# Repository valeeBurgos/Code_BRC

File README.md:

# Code_BRC

Placa y código funcional pero con ciertos fallos  para un robot velocista.

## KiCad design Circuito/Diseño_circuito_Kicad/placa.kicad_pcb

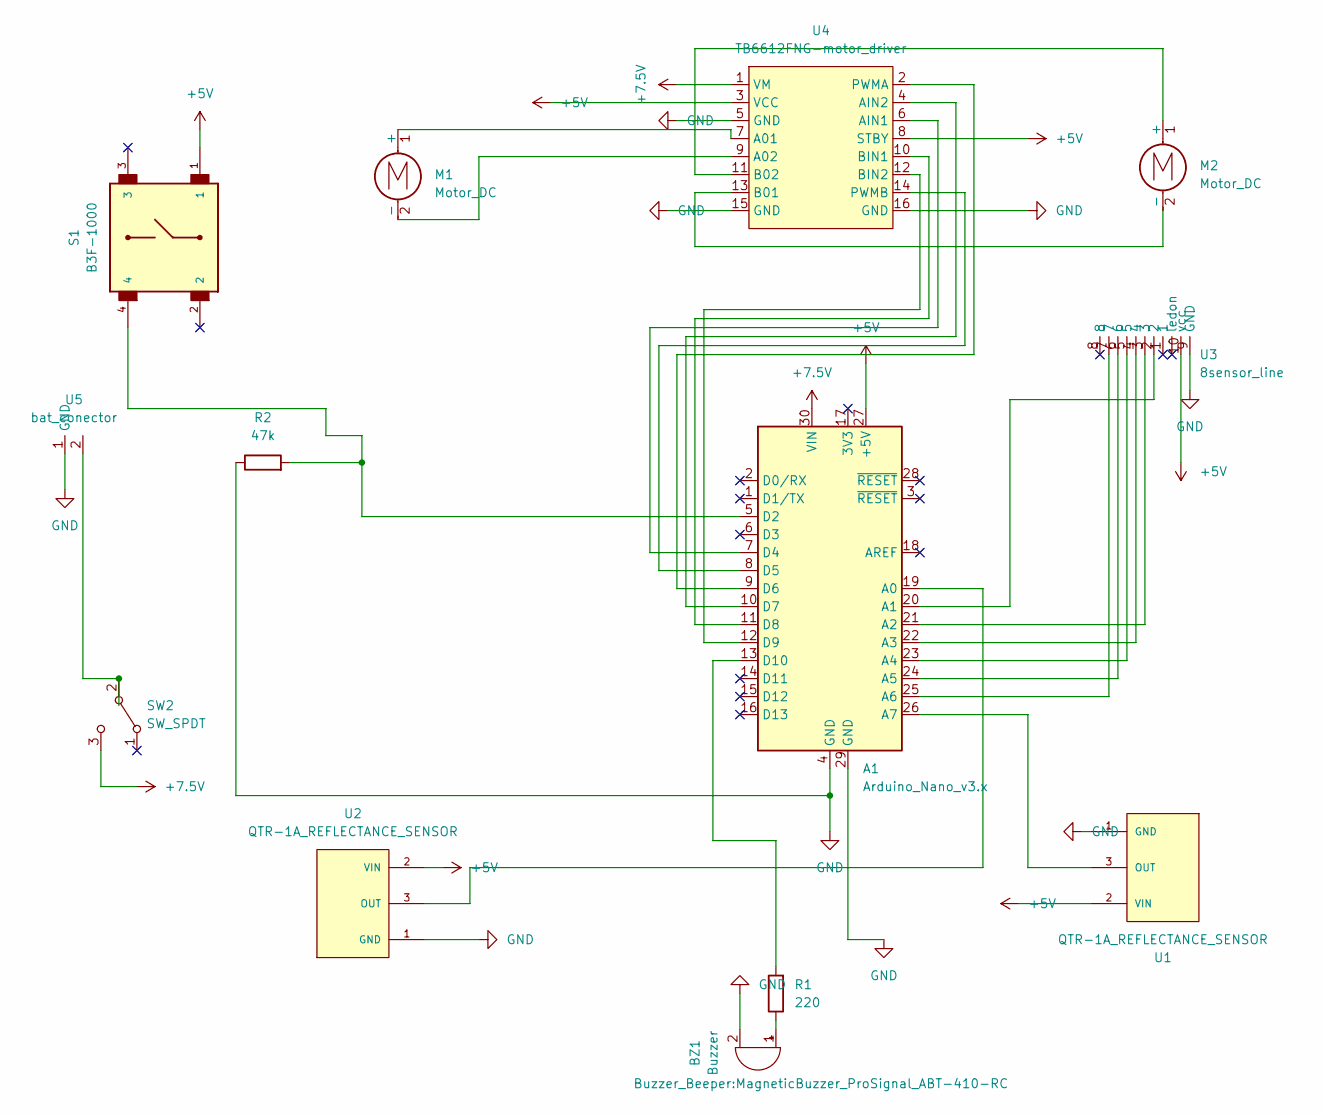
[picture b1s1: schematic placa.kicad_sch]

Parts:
A1: Arduino_Nano_v3.x; Arduino_Nano
BZ1: Buzzer; MagneticBuzzer_ProSignal_ABT-410-RC
M1, M2: Motor_DC; motor dc conection_copy
R1: 220; R_Axial_DIN0207_L6.3mm_D2.5mm_P15.24mm_Horizontal
R2: 47k; R_Axial_DIN0207_L6.3mm_D2.5mm_P15.24mm_Horizontal
S1: B3F-1000; SW_B3F-1000
SW2: SW_SPDT; SPST slide switch
U1, U2: QTR-1A_REFLECTANCE_SENSOR; SENSOR_QTR-1A_REFLECTANCE_SENSOR
U3: 8sensor_line; 8-lines sensor
U4: TB6612FNG-motor_driver; TB6612FNG-Motor driver
U5: bat_conector; motor dc conection_copy

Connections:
+5V: A1.27 (+5V), S1.1, U1.2 (VIN), U2.2 (VIN), U3.10 (vcc), U4.3 (VCC), U4.8 (STBY)
+7.5V: A1.30 (VIN), SW2.3 (C), U4.1 (VM)
GND: A1.4 (GND), A1.29 (GND), BZ1.2 (+), R2.1, U1.1 (GND), U2.1 (GND), U3.9 (GND), U4.5 (GND), U4.15 (GND), U4.16 (GND), U5.1 (GND)
unnamed: A1.5 (D2), R2.2, S1.4
unnamed: A1.7 (D4), U4.6 (AIN1)
unnamed: A1.8 (D5), U4.14 (PWMB)
unnamed: A1.9 (D6), U4.2 (PWMA)
unnamed: A1.10 (D7), U4.4 (AIN2)
unnamed: A1.11 (D8), U4.10 (BIN1)
unnamed: A1.12 (D9), U4.12 (BIN2)
unnamed: A1.13 (D10), R1.2
unnamed: A1.19 (A0), U2.3 (OUT)
unnamed: A1.20 (A1), U3.2
unnamed: A1.21 (A2), U3.3
unnamed: A1.22 (A3), U3.4
unnamed: A1.23 (A4), U3.5
unnamed: A1.24 (A5), U3.6
unnamed: A1.25 (A6), U3.7
unnamed: A1.26 (A7), U1.3 (OUT)
unnamed: BZ1.1 (-), R1.1
unnamed: M1.1 (+), U4.7 (A01)
unnamed: M1.2 (-), U4.9 (A02)
unnamed: M2.1 (+), U4.11 (B02)
unnamed: M2.2 (-), U4.13 (B01)
unnamed: SW2.2 (B), U5.2

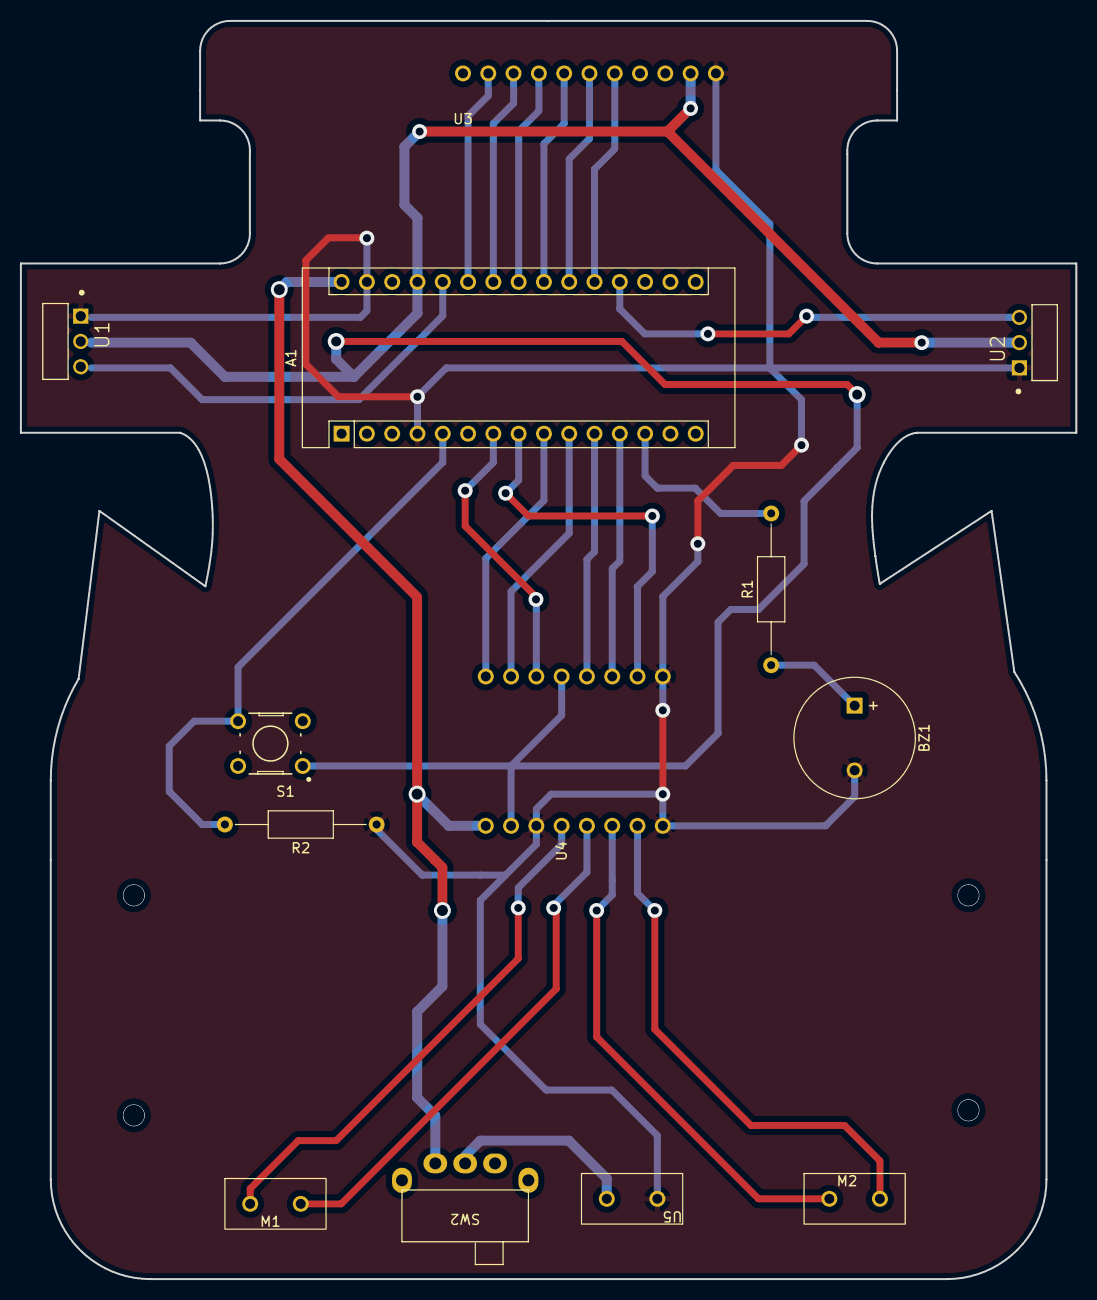
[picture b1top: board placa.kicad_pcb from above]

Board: 2 copper layers, 106.0 x 126.4 mm, 13 parts (0 on the bottom side), 25 nets.

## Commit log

2022-10-28 Codigo inicial basico, solo sigue linea
2022-10-28 Se agregó circuito kicad
2022-10-28 Actualizacion a main
2022-11-07 change code
2022-11-09 corre, al menos
2022-11-09 para
2022-11-10 intento 2, velocidad 52
2022-11-11 code para final
